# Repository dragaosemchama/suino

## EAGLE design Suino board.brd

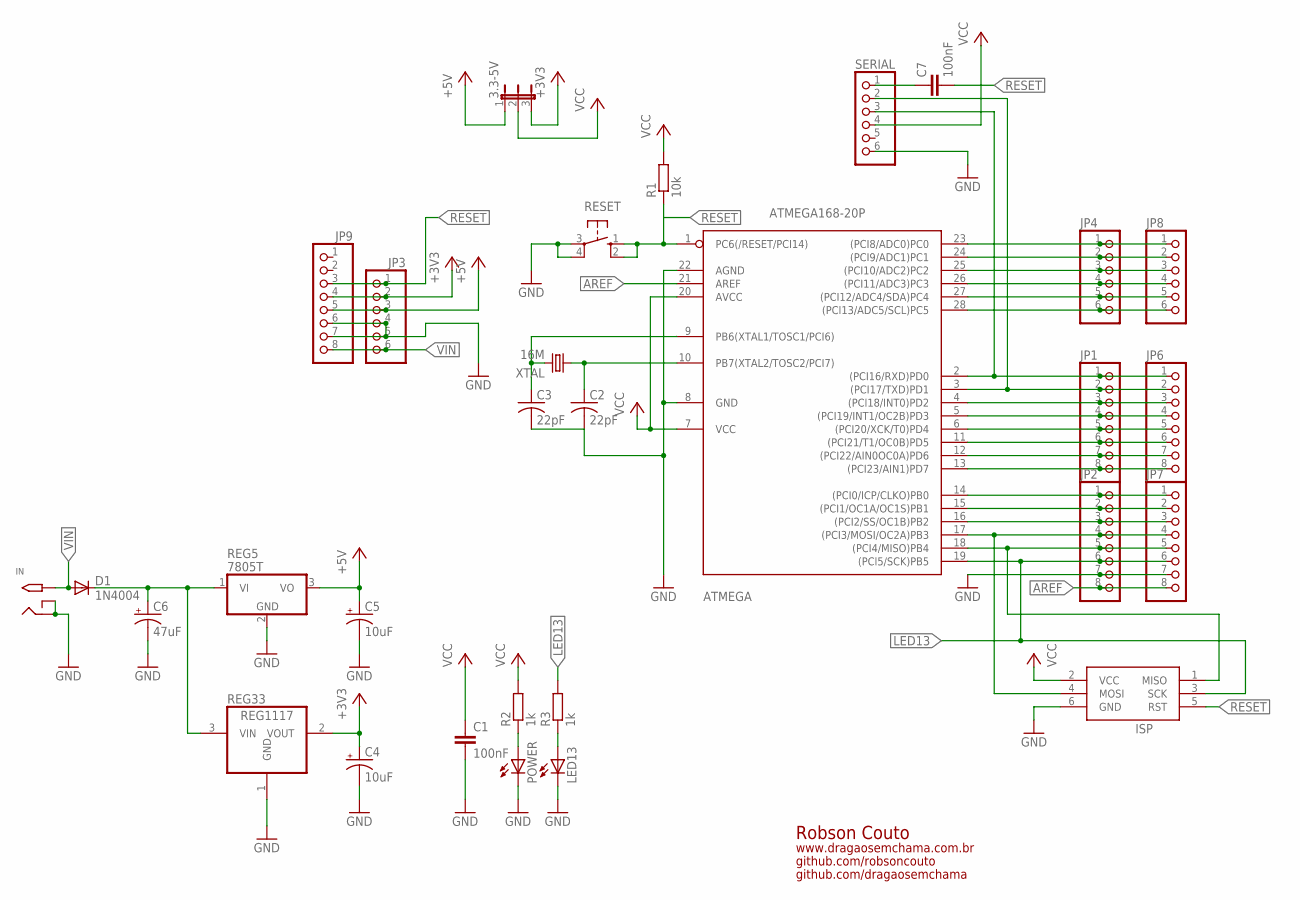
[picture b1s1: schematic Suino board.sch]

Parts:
3.3-5V: JP2E; JP2
ATMEGA: ATMEGA168-20P; DIL28-3
C1, C7: 100nF; C050-025X075
C2, C3: 22pF; C025-030X050
C4, C5: 10uF; E2,5-5
C6: 47uF; E2,5-6
D1: 1N4004; DO41-10
IN: 2.1MMJACKTHM; PJ-102A
ISP: AVRISP-6; AVRISP
JP1, JP2, JP6, JP7, JP9: PINHD-1X8BIG; 1X08-BIG
JP3, JP4, JP8: PINHD-1X6B; 1X06-BIG
LED13: LED3MM
POWER: LED3MM
R1: 10k; 0207/7
R2, R3: 1k; 0207/7
REG5: 7805T; TO220H
REG33: REG1117; SOT223
RESET: 10-XX; B3F-10XX
SERIAL: PINHD-1X6; 1X06
XTAL: 16M; HC49/S

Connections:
+3V3: 3.3-5V.3, C4.+, JP3.2, JP9.4, REG33.2 (VOUT)
+5V: 3.3-5V.1, C5.+, JP3.3, JP9.5, REG5.3 (VO)
AREF: ATMEGA.21 (AREF), JP2.8, JP7.8
GND: ATMEGA.8 (GND), ATMEGA.22 (AGND), C1.2, C2.2, C3.2, C4.-, C5.-, C6.-, IN.RING, IN.RING_SW, ISP.6 (GND), JP2.7, JP3.4, JP3.5, JP7.7, JP9.6, JP9.7, LED13.K (C), POWER.K (C), REG5.2 (GND), REG33.1 (GND), RESET.3, RESET.4 (P1), SERIAL.6
LED13: ATMEGA.19 ((PCI5/SCK)PB5), ISP.3 (SCK), JP2.6, JP7.6, R3.2
unnamed: C7.1, SERIAL.1
unnamed: ATMEGA.9 (PB6(XTAL1/TOSC1/PCI6)), C3.1, XTAL.2
unnamed: ATMEGA.10 (PB7(XTAL2/TOSC2/PCI7)), C2.1, XTAL.1
unnamed: POWER.A, R2.1
unnamed: LED13.A, R3.1
unnamed: ATMEGA.23 ((PCI8/ADC0)PC0), JP4.1, JP8.1
unnamed: ATMEGA.24 ((PCI9/ADC1)PC1), JP4.2, JP8.2
unnamed: ATMEGA.25 ((PCI10/ADC2)PC2), JP4.3, JP8.3
unnamed: ATMEGA.26 ((PCI11/ADC3)PC3), JP4.4, JP8.4
unnamed: ATMEGA.27 ((PCI12/ADC4/SDA)PC4), JP4.5, JP8.5
unnamed: ATMEGA.28 ((PCI13/ADC5/SCL)PC5), JP4.6, JP8.6
unnamed: ATMEGA.2 ((PCI16/RXD)PD0), JP1.1, JP6.1, SERIAL.3
unnamed: ATMEGA.3 ((PCI17/TXD)PD1), JP1.2, JP6.2, SERIAL.2
unnamed: ATMEGA.4 ((PCI18/INT0)PD2), JP1.3, JP6.3
unnamed: ATMEGA.5 ((PCI19/INT1/OC2B)PD3), JP1.4, JP6.4
unnamed: ATMEGA.6 ((PCI20/XCK/T0)PD4), JP1.5, JP6.5
unnamed: ATMEGA.11 ((PCI21/T1/OC0B)PD5), JP1.6, JP6.6
unnamed: ATMEGA.12 ((PCI22/AIN0OC0A)PD6), JP1.7, JP6.7
unnamed: ATMEGA.13 ((PCI23/AIN1)PD7), JP1.8, JP6.8
unnamed: ATMEGA.14 ((PCI0/ICP/CLKO)PB0), JP2.1, JP7.1
unnamed: ATMEGA.15 ((PCI1/OC1A/OC1S)PB1), JP2.2, JP7.2
unnamed: ATMEGA.16 ((PCI2/SS/OC1B)PB2), JP2.3, JP7.3
unnamed: ATMEGA.17 ((PCI3/MOSI/OC2A)PB3), ISP.4 (MOSI), JP2.4, JP7.4
unnamed: ATMEGA.18 ((PCI4/MISO)PB4), ISP.1 (MISO), JP2.5, JP7.5
RESET: ATMEGA.1 (PC6(/RESET/PCI14)), C7.2, ISP.5 (RST), JP3.1, JP9.3, R1.1, RESET.1 (S), RESET.2 (S1)
VCC: 3.3-5V.2, ATMEGA.7 (VCC), ATMEGA.20 (AVCC), C1.1, ISP.2 (VCC), R1.2, R2.2, SERIAL.4
VD: C6.+, D1.C, REG5.1 (VI), REG33.3 (VIN)
VIN: D1.A, IN.TIP, JP3.6, JP9.8

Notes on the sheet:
Robson Couto
www.dragaosemchama.com.br
github.com/robsoncouto
github.com/dragaosemchama

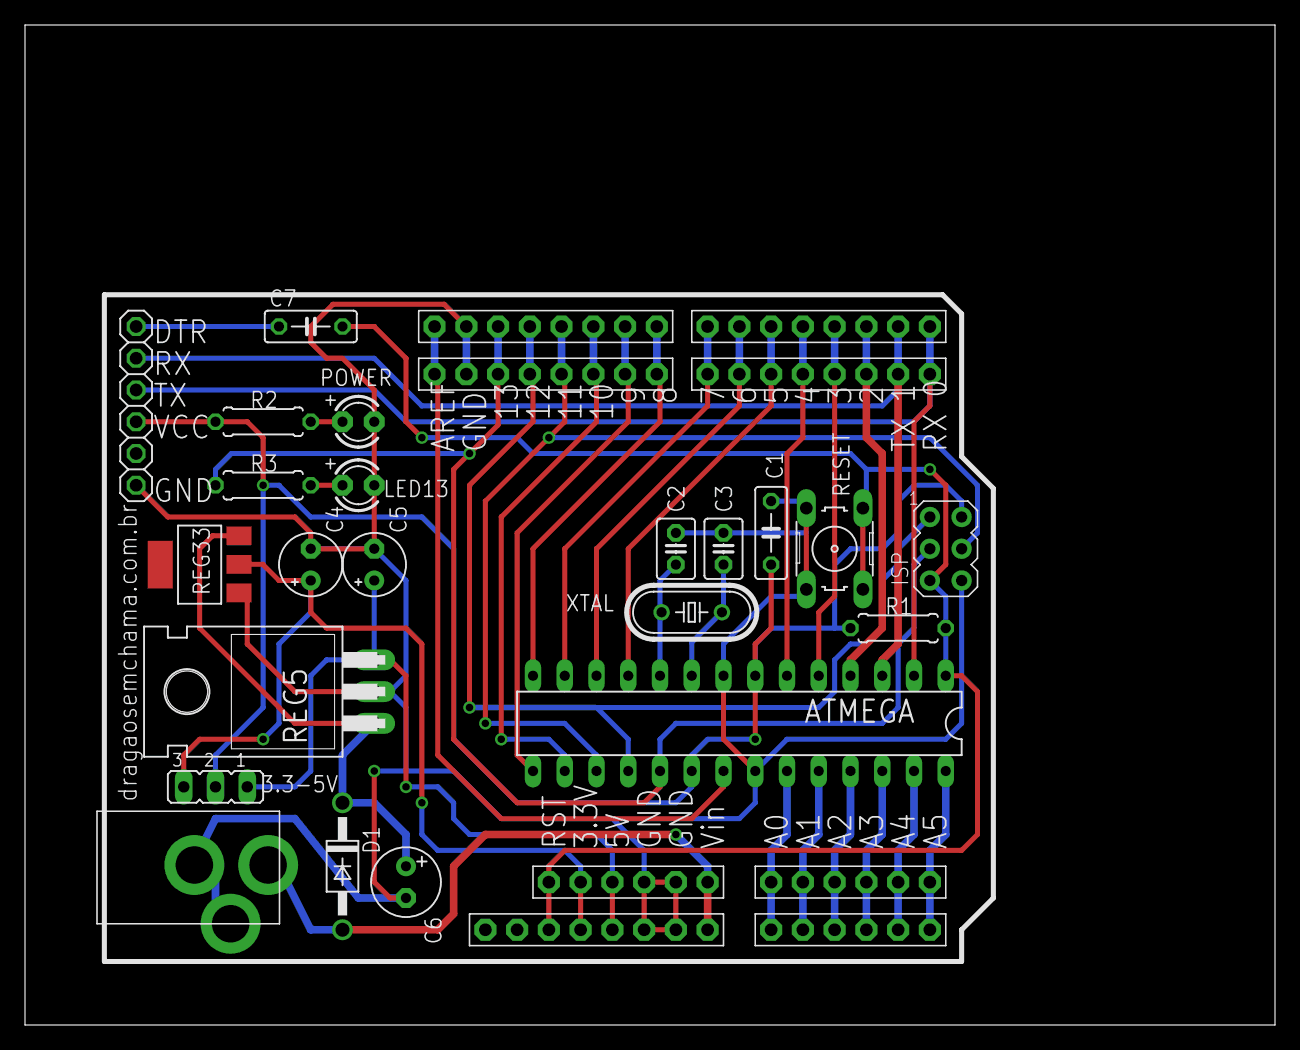
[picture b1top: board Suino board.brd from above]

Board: 2 copper layers, 100.0 x 80.0 mm, 30 parts (0 on the bottom side), 33 nets.

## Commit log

2017-04-18 Added eagle files to repo
    Started working on project. Created a schematic file and still have to
    draw the board layout
2017-04-18 Small fixes
    Added a serial port header and LEDs for on and pin 13
2017-04-19 Fixes in net names and the voltage input jack
2017-04-19 Fixed some things in schematic and started working on layout
2017-04-20 Finished layout, still needs cleaning
2017-04-20 No drc errors
2017-04-21 First version
2017-04-21 Create LICENSE
2017-04-24 Added frame and name
